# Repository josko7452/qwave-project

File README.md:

QWave-project
=============

Working FPGA development board with USB 2.0 interface and DSO module (125MHz analog dual channel with 16bit logic analyzer)
Although hadware was implemented it is not thoroughly tested, especially analog part is not intented as ready to build kit, it is inteded for hackers and people who are wiling to play around to get it working.

# Project parts
* **hardware** design sources of FPGA developement board and DSO module in eagle
* **firmware** sources of FPGA firmware in MyHDL and translated VHDL Xinix ISE project directory
* **software** sources of Qt based DSO sampling software

# Preview
## FPGA dev board and DSO module (dimensions 10x4cm):
-
## Software
[Screenshot gallery](http://imgur.com/a/RICwH#0)

#Schematics
[Link to PDF](https://www.dropbox.com/sh/cy4ldah24slzdpa/zRzbHfkyo1)

#Details:
## FPGA board:
### What works:
* FPGA programming and 3.3V logic interface and FT245 Sync interface (USB 2.0 speed)

### TODO:
* Direct USB programming of FPGA flash - need to use JTAG and Xilinx USB Platform Cable for programming

## Analog (DSO module) board:
### What works:
* DSO functionality

### What was not tested:
* Logic analyzer on anything faster than few kHz
* Compensation of analog input

### TODO:
* Eliminating noise on analog circuits

## Firmware
### TODO:
* Fix trigger
* Add selectable trigger holdoff
* Do not insert trigger in single-shot mode

## Software
### TODO:
* Better performance
* Make more user-friendly selection of trigger
* Add exact voltage meter

## For hackers/ee guys and developers:
See HACKING.md

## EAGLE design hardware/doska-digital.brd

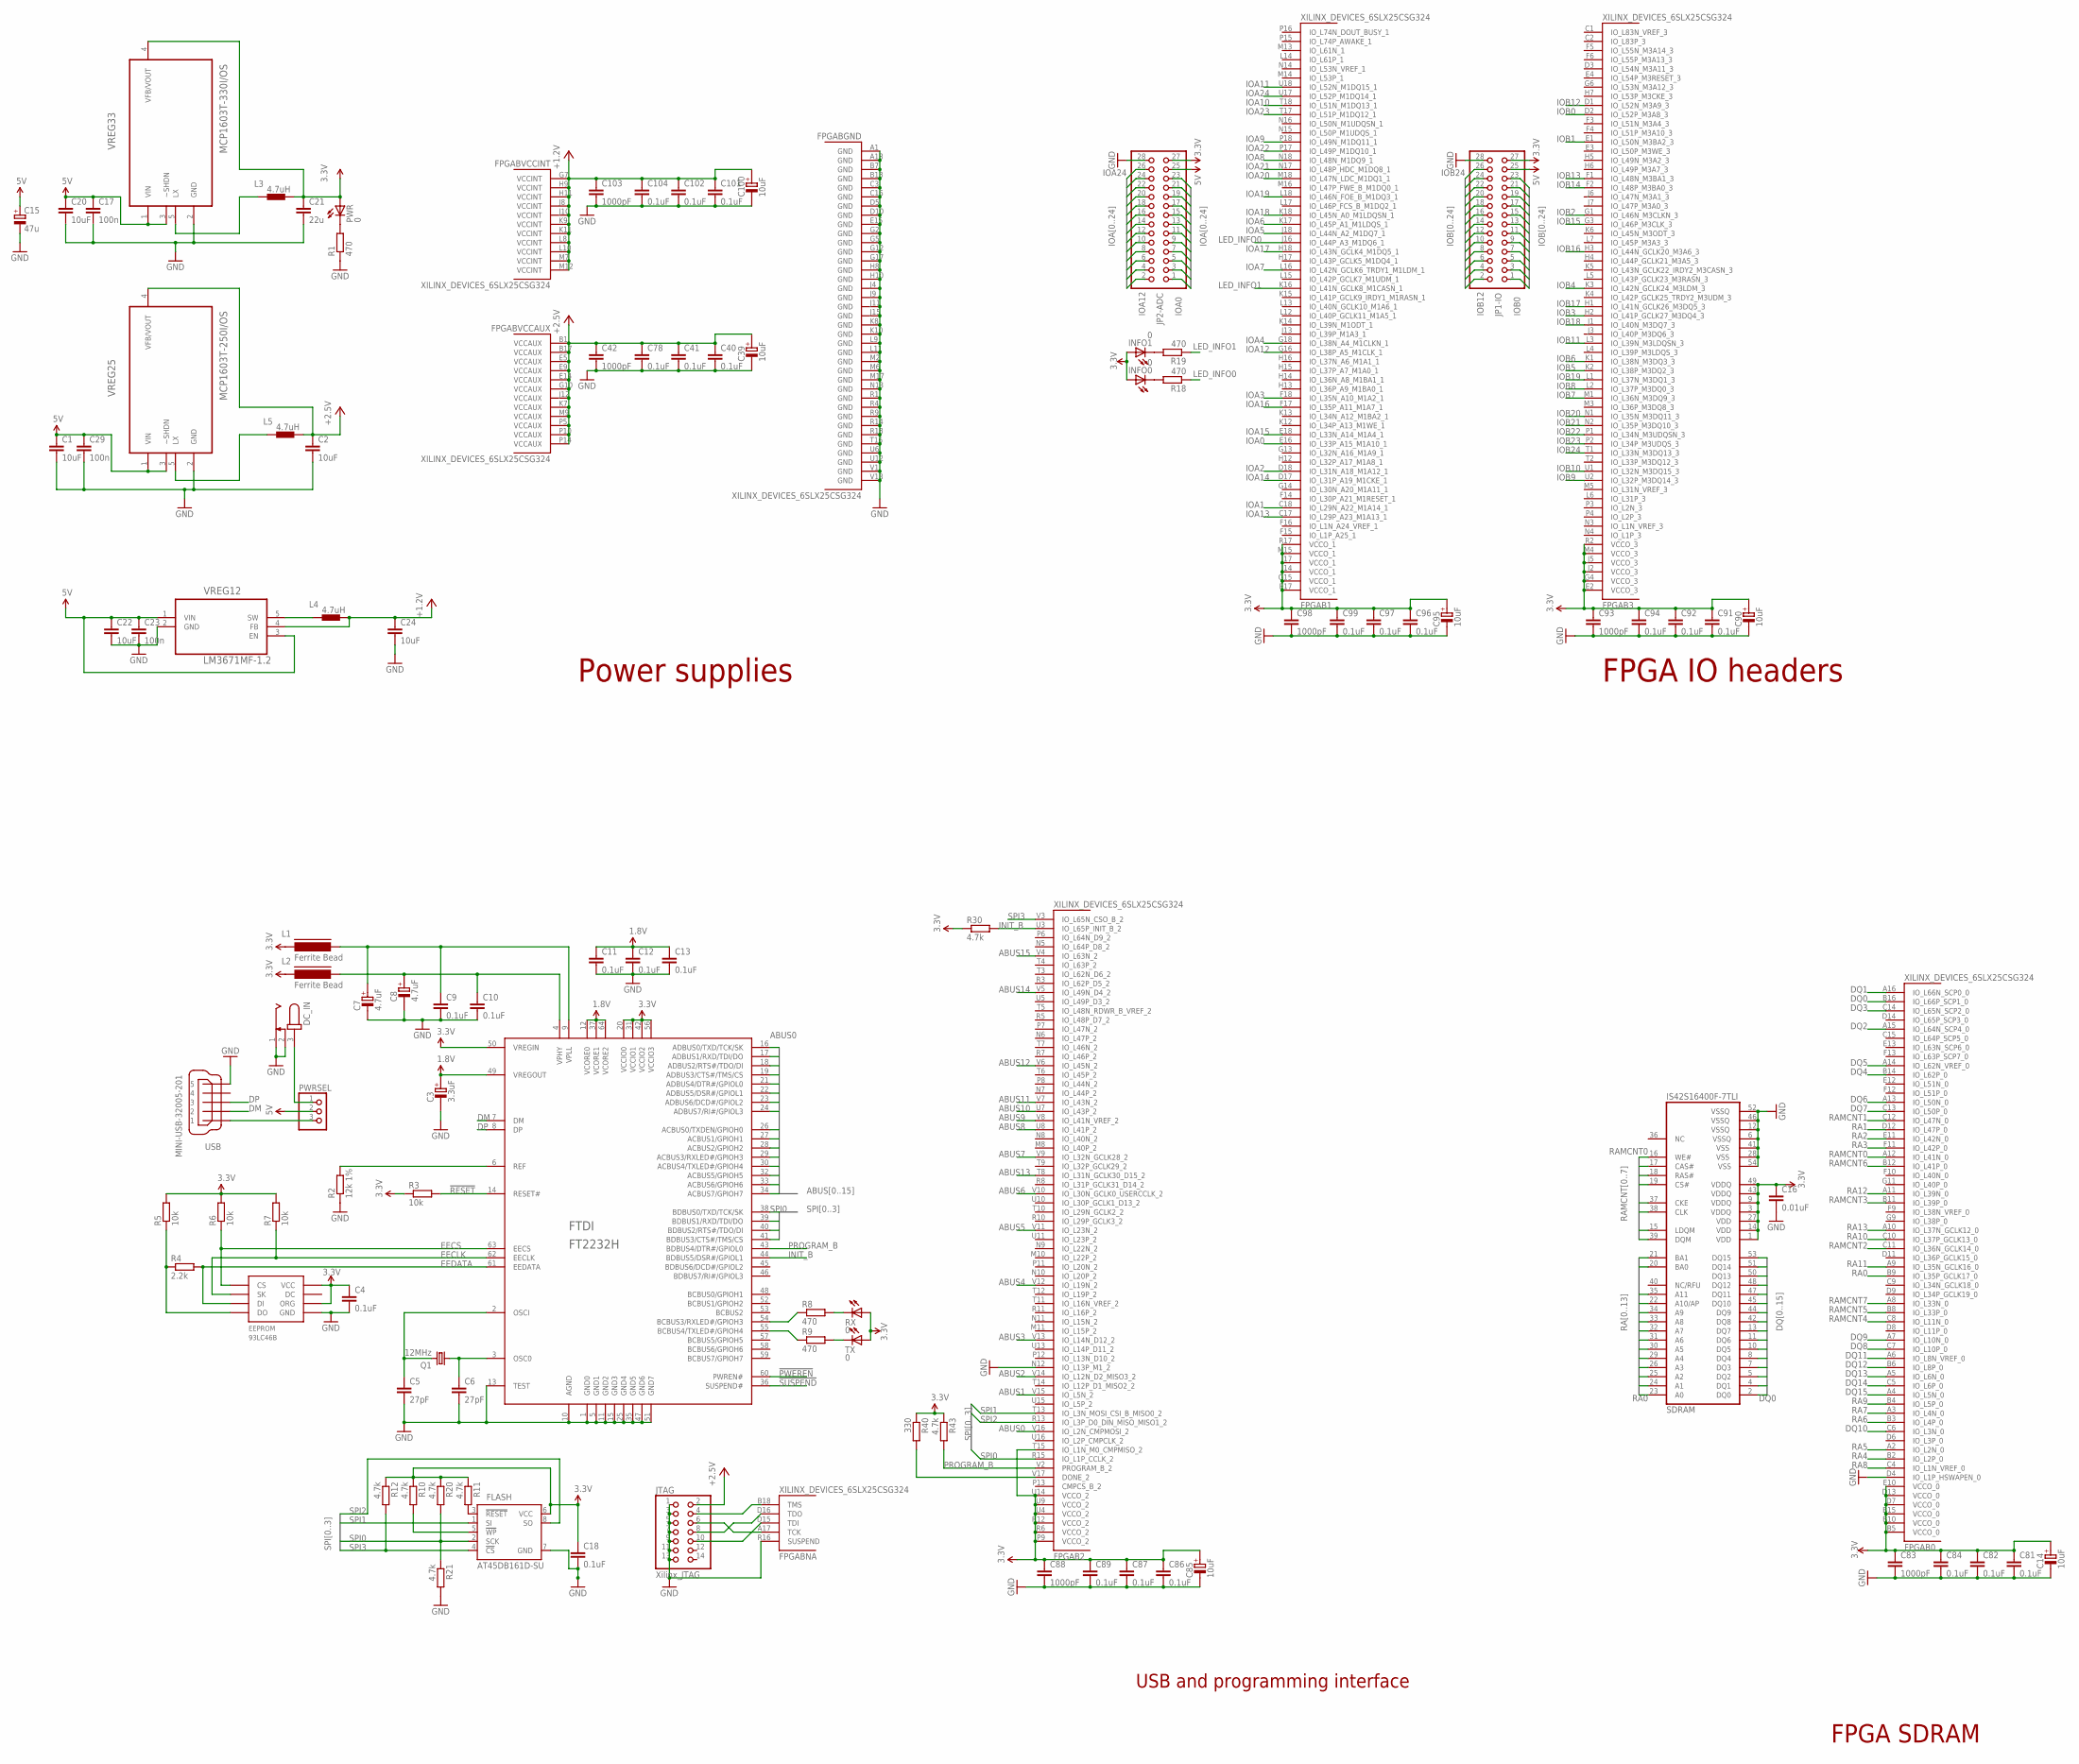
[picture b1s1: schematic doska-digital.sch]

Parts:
C1, C2, C20, C22, C24: 10uF; C805
C3: 3.3uF; CAPMP3216X180N
C4, C13, C18: 0.1uF; C805
C5, C6: 27pF; C805
C7, C8: 4.7uF; CAPMP3216X180N
C9, C10, C11, C12, C40, C41, C78, C81, C82, C84, C86, C87, C89, C91, C92, C94, C96, C97, C99, C101, C102, C104: 0.1uF; C603
C14, C39, C85, C90, C95, C100: 10uF; CAPMP3216X180N
C15: 47u; RCL_E2-5
C16: 0.01uF; C805
C17, C23, C29: 100n; C805
C21: 22u; C805
C42, C83, C88, C93, C98, C103: 1000pF; C603
DC_IN: CON-JACK_JACK-PLUG1; CON-JACK_SPC4078
EEPROM: 93LC46B; SOIC8
FLASH: AT45DB161D-SU; 8S2
FPGA: XILINX_DEVICES_6SLX25CSG324; XILINX_DEVICES_CS324
FTDI: FT2232H; LQFP64
INFO0, INFO1: 0; CHIPLED_1206
JP1-IO, JP2-ADC: PINHEAD_PINHD-2X14; PINHEAD_2X14
JTAG: Xilinx_JTAG; PINHEAD_2X07
L1, L2: Ferrite Bead; FB805
L3, L4, L5: 4.7uH; SMT43
PWR: 0; CHIPLED_1206
PWRSEL: PINHEAD_PINHD-1X3; PINHEAD_1X03
Q1: 12MHz; CTS406
R1, R8, R9, R18, R19: 470; R805
R2: 12k 1%; R603
R3, R5, R6, R7: 10k; R805
R4: 2.2k; R805
R10, R11, R12: 4.7k; R805
R20, R21, R30, R43: 4.7k; R603
R40: 330; R603
RX: 0; CHIPLED_1206
SDRAM: IS42S16400F-7TLI; TSOP54
TX: 0; CHIPLED_1206
USB: MINI-USB-32005-201; 32005-201
VREG12: LM3671MF-1.2; SOT95P284X122-5N
VREG25: MCP1603T-250I/OS; SOT95P280X110-5N
VREG33: MCP1603T-330I/OS; SOT95P280X110-5N

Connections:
1.8V: C3.+, C11.1, C12.1, C13.1, FTDI.12 (VCORE0), FTDI.37 (VCORE1), FTDI.49 (VREGOUT), FTDI.64 (VCORE2)
3.3V: C4.1, C14.+, C16.1, C18.1, C21.1, C81.1, C82.1, C83.1, C84.1, C85.+, C86.1, C87.1, C88.1, C89.1, C90.+, C91.1, C92.1, C93.1, C94.1, C95.+, C96.1, C97.1, C98.1, C99.1, EEPROM.6 (ORG), EEPROM.8 (VCC), FLASH.6 (VCC), FPGA.B5 (VCCO_0), FPGA.B10 (VCCO_0), FPGA.B15 (VCCO_0), FPGA.D7 (VCCO_0), FPGA.D13 (VCCO_0), FPGA.E2 (VCCO_3), FPGA.E10 (VCCO_0), FPGA.E17 (VCCO_1), FPGA.G4 (VCCO_3), FPGA.G15 (VCCO_1), FPGA.J2 (VCCO_3), FPGA.J5 (VCCO_3), FPGA.J14 (VCCO_1), FPGA.J17 (VCCO_1), FPGA.M4 (VCCO_3), FPGA.M15 (VCCO_1), FPGA.P9 (VCCO_2), FPGA.R2 (VCCO_3), FPGA.R6 (VCCO_2), FPGA.R12 (VCCO_2), FPGA.R17 (VCCO_1), FPGA.T15 (IO_L1N_M0_CMPMISO_2), FPGA.U4 (VCCO_2), FPGA.U9 (VCCO_2), FPGA.U14 (VCCO_2), FTDI.20 (VCCIO0), FTDI.31 (VCCIO1), FTDI.42 (VCCIO2), FTDI.50 (VREGIN), FTDI.56 (VCCIO3), INFO0.A, INFO1.A, JP1-IO.27, JP2-ADC.27, L1.2, L2.2, L3.P$1 (1), PWR.A, R3.1, R5.2, R6.2, R7.2, R10.1, R11.1, R12.1, R20.1, R30.1, R40.1, R43.1, RX.A, SDRAM.1 (VDD), SDRAM.3 (VDDQ), SDRAM.9 (VDDQ), SDRAM.14 (VDD), SDRAM.27 (VDD), SDRAM.43 (VDDQ), SDRAM.49 (VDDQ), TX.A, VREG33.4 (VFB/VOUT)
5V: C1.1, C15.+, C17.1, C20.1, C22.1, C23.1, C29.1, JP1-IO.25, JP2-ADC.25, PWRSEL.2, VREG12.1 (VIN), VREG12.3 (EN), VREG25.1 (VIN), VREG25.3 (~SHDN), VREG33.1 (VIN), VREG33.3 (~SHDN)
!PWEREN: FTDI.60 (PWREN#)
!RESET: FTDI.14 (RESET#), R3.2
!SUSPEND: FTDI.36 (SUSPEND#)
+1.2V: C24.1, C100.+, C101.1, C102.1, C103.1, C104.1, FPGA.G7 (VCCINT), FPGA.H9 (VCCINT), FPGA.H11 (VCCINT), FPGA.J8 (VCCINT), FPGA.J10 (VCCINT), FPGA.K9 (VCCINT), FPGA.K11 (VCCINT), FPGA.L8 (VCCINT), FPGA.L10 (VCCINT), FPGA.M7 (VCCINT), FPGA.M12 (VCCINT), L4.P$1 (1), VREG12.4 (FB)
+2.5V: C2.1, C39.+, C40.1, C41.1, C42.1, C78.1, FPGA.B1 (VCCAUX), FPGA.B17 (VCCAUX), FPGA.E5 (VCCAUX), FPGA.E9 (VCCAUX), FPGA.E14 (VCCAUX), FPGA.G10 (VCCAUX), FPGA.J12 (VCCAUX), FPGA.K7 (VCCAUX), FPGA.M9 (VCCAUX), FPGA.P5 (VCCAUX), FPGA.P10 (VCCAUX), FPGA.P14 (VCCAUX), JTAG.2, L5.P$1 (1), VREG25.4 (VFB/VOUT)
ABUS0: FPGA.V16 (IO_L2N_CMPMOSI_2), FTDI.16 (ADBUS0/TXD/TCK/SK)
ABUS1: FPGA.V15 (IO_L5N_2), FTDI.17 (ADBUS1/RXD/TDI/DO)
ABUS2: FPGA.V14 (IO_L12N_D2_MISO3_2), FTDI.18 (ADBUS2/RTS#/TDO/DI)
ABUS3: FPGA.V13 (IO_L14N_D12_2), FTDI.19 (ADBUS3/CTS#/TMS/CS)
ABUS4: FPGA.V12 (IO_L19N_2), FTDI.21 (ADBUS4/DTR#/GPIOL0)
ABUS5: FPGA.V11 (IO_L23N_2), FTDI.22 (ADBUS5/DSR#/GPIOL1)
ABUS6: FPGA.V10 (IO_L30N_GCLK0_USERCCLK_2), FTDI.23 (ADBUS6/DCD#/GPIOL2)
ABUS7: FPGA.V9 (IO_L32N_GCLK28_2), FTDI.24 (ADBUS7/RI#/GPIOL3)
ABUS8: FPGA.U8 (IO_L41P_2), FTDI.26 (ACBUS0/TXDEN/GPIOH0)
ABUS9: FPGA.V8 (IO_L41N_VREF_2), FTDI.27 (ACBUS1/GPIOH1)
ABUS10: FPGA.U7 (IO_L43P_2), FTDI.28 (ACBUS2/GPIOH2)
ABUS11: FPGA.V7 (IO_L43N_2), FTDI.29 (ACBUS3/RXLED#/GPIOH3)
ABUS12: FPGA.V6 (IO_L45N_2), FTDI.30 (ACBUS4/TXLED#/GPIOH4)
ABUS13: FPGA.T8 (IO_L31N_GCLK30_D15_2), FTDI.32 (ACBUS5/GPIOH5)
ABUS14: FPGA.V5 (IO_L49N_D4_2), FTDI.33 (ACBUS6/GPIOH6)
ABUS15: FPGA.V4 (IO_L63N_2), FTDI.34 (ACBUS7/GPIOH7)
DM: FTDI.7 (DM), USB.2
DP: FTDI.8 (DP), USB.3
DQ0: FPGA.B16 (IO_L66P_SCP1_0), SDRAM.2 (DQ0)
DQ1: FPGA.A16 (IO_L66N_SCP0_0), SDRAM.4 (DQ1)
DQ2: FPGA.A15 (IO_L64N_SCP4_0), SDRAM.5 (DQ2)
DQ3: FPGA.C14 (IO_L65N_SCP2_0), SDRAM.7 (DQ3)
DQ4: FPGA.B14 (IO_L62P_0), SDRAM.8 (DQ4)
DQ5: FPGA.A14 (IO_L62N_VREF_0), SDRAM.10 (DQ5)
DQ6: FPGA.A13 (IO_L50N_0), SDRAM.11 (DQ6)
DQ7: FPGA.C13 (IO_L50P_0), SDRAM.13 (DQ7)
DQ8: FPGA.C7 (IO_L10P_0), SDRAM.42 (DQ8)
DQ9: FPGA.A7 (IO_L10N_0), SDRAM.44 (DQ9)
DQ10: FPGA.C6 (IO_L3N_0), SDRAM.45 (DQ10)
DQ11: FPGA.A6 (IO_L8N_VREF_0), SDRAM.47 (DQ11)
DQ12: FPGA.B6 (IO_L8P_0), SDRAM.48 (DQ12)
DQ13: FPGA.A5 (IO_L6N_0), SDRAM.50 (DQ13)
DQ14: FPGA.C5 (IO_L6P_0), SDRAM.51 (DQ14)
DQ15: FPGA.A4 (IO_L5N_0), SDRAM.53 (DQ15)
EECLK: EEPROM.2 (SK), FTDI.62 (EECLK), R7.1
EECS: EEPROM.1 (CS), FTDI.63 (EECS), R6.1
EEDATA: EEPROM.3 (DI), FTDI.61 (EEDATA), R4.2
GND: C1.2, C2.2, C3.-, C4.2, C5.2, C6.2, C7.-, C8.-, C9.2, C10.2, C11.2, C12.2, C13.2, C14.-, C15.-, C16.2, C17.2, C18.2, C20.2, C21.2, C22.2, C23.2, C24.2, C29.2, C39.-, C40.2, C41.2, C42.2, C78.2, C81.2, C82.2, C83.2, C84.2, C85.-, C86.2, C87.2, C88.2, C89.2, C90.-, C91.2, C92.2, C93.2, C94.2, C95.-, C96.2, C97.2, C98.2, C99.2, C100.-, C101.2, C102.2, C103.2, C104.2, DC_IN.1, DC_IN.2, EEPROM.5 (GND), FLASH.7 (GND), FPGA.A1 (GND), FPGA.A18 (GND), FPGA.B7 (GND), FPGA.B13 (GND), FPGA.C3 (GND), FPGA.C16 (GND), FPGA.D4 (IO_L1P_HSWAPEN_0), FPGA.D5 (GND), FPGA.D10 (GND), FPGA.E15 (GND), FPGA.G2 (GND), FPGA.G5 (GND), FPGA.G12 (GND), FPGA.G17 (GND), FPGA.H8 (GND), FPGA.H10 (GND), FPGA.J4 (GND), FPGA.J9 (GND), FPGA.J11 (GND), FPGA.J15 (GND), FPGA.K8 (GND), FPGA.K10 (GND), FPGA.L9 (GND), FPGA.L11 (GND), FPGA.M2 (GND), FPGA.M6 (GND), FPGA.M17 (GND), FPGA.N12 (IO_L13P_M1_2), FPGA.N13 (GND), FPGA.R1 (GND), FPGA.R4 (GND), FPGA.R9 (GND), FPGA.R14 (GND), FPGA.R16 (SUSPEND), FPGA.R18 (GND), FPGA.T16 (GND), FPGA.U6 (GND), FPGA.U12 (GND), FPGA.V1 (GND), FPGA.V18 (GND), FTDI.1 (GND0), FTDI.5 (GND1), FTDI.10 (AGND), FTDI.11 (GND2), FTDI.13 (TEST), FTDI.15 (GND3), FTDI.25 (GND4), FTDI.35 (GND5), FTDI.47 (GND6), FTDI.51 (GND7), JP1-IO.28, JP2-ADC.28, JTAG.1, JTAG.3, JTAG.5, JTAG.7, JTAG.9, JTAG.11, JTAG.13, R1.1, R2.1, R21.2, SDRAM.6 (VSSQ), SDRAM.12 (VSSQ), SDRAM.28 (VSS), SDRAM.41 (VSS), SDRAM.46 (VSSQ), SDRAM.52 (VSSQ), SDRAM.54 (VSS), USB.5, VREG12.2 (GND), VREG25.2 (GND), VREG33.2 (GND)
INIT_B: FPGA.U3 (IO_L65P_INIT_B_2), FTDI.44 (BDBUS5/DSR#/GPIOL1), R30.2
IOA0: FPGA.E16 (IO_L33P_A15_M1A10_1), JP2-ADC.1
IOA1: FPGA.C18 (IO_L29N_A22_M1A14_1), JP2-ADC.3
IOA2: FPGA.D18 (IO_L31N_A18_M1A12_1), JP2-ADC.5
IOA3: FPGA.F18 (IO_L35N_A10_M1A2_1), JP2-ADC.7
IOA4: FPGA.G18 (IO_L38N_A4_M1CLKN_1), JP2-ADC.9
IOA5: FPGA.J18 (IO_L44N_A2_M1DQ7_1), JP2-ADC.11
IOA6: FPGA.K17 (IO_L45P_A1_M1LDQS_1), JP2-ADC.13
IOA7: FPGA.L16 (IO_L42N_GCLK6_TRDY1_M1LDM_1), JP2-ADC.15
IOA8: FPGA.N18 (IO_L48N_M1DQ9_1), JP2-ADC.17
IOA9: FPGA.P18 (IO_L49N_M1DQ11_1), JP2-ADC.19
IOA10: FPGA.T18 (IO_L51N_M1DQ13_1), JP2-ADC.21
IOA11: FPGA.U18 (IO_L52N_M1DQ15_1), JP2-ADC.23
IOA12: FPGA.G16 (IO_L38P_A5_M1CLK_1), JP2-ADC.2
IOA13: FPGA.C17 (IO_L29P_A23_M1A13_1), JP2-ADC.4
IOA14: FPGA.D17 (IO_L31P_A19_M1CKE_1), JP2-ADC.6
IOA15: FPGA.E18 (IO_L33N_A14_M1A4_1), JP2-ADC.8
IOA16: FPGA.F17 (IO_L35P_A11_M1A7_1), JP2-ADC.10
IOA17: FPGA.H18 (IO_L43N_GCLK4_M1DQ5_1), JP2-ADC.12
IOA18: FPGA.K18 (IO_L45N_A0_M1LDQSN_1), JP2-ADC.14
IOA19: FPGA.L18 (IO_L46N_FOE_B_M1DQ3_1), JP2-ADC.16
IOA20: FPGA.M18 (IO_L47N_LDC_M1DQ1_1), JP2-ADC.18
IOA21: FPGA.N17 (IO_L48P_HDC_M1DQ8_1), JP2-ADC.20
IOA22: FPGA.P17 (IO_L49P_M1DQ10_1), JP2-ADC.22
IOA23: FPGA.T17 (IO_L51P_M1DQ12_1), JP2-ADC.24
IOA24: FPGA.U17 (IO_L52P_M1DQ14_1), JP2-ADC.26
IOB0: FPGA.D2 (IO_L52P_M3A8_3), JP1-IO.1
IOB1: FPGA.E1 (IO_L50N_M3BA2_3), JP1-IO.3
IOB2: FPGA.G1 (IO_L46N_M3CLKN_3), JP1-IO.5
IOB3: FPGA.H2 (IO_L41P_GCLK27_M3DQ4_3), JP1-IO.7
IOB4: FPGA.K3 (IO_L42N_GCLK24_M3LDM_3), JP1-IO.9
IOB5: FPGA.K2 (IO_L38P_M3DQ2_3), JP1-IO.11
IOB6: FPGA.K1 (IO_L38N_M3DQ3_3), JP1-IO.13
IOB7: FPGA.M1 (IO_L36N_M3DQ9_3), JP1-IO.15
IOB8: FPGA.L2 (IO_L37P_M3DQ0_3), JP1-IO.17
IOB9: FPGA.U2 (IO_L32P_M3DQ14_3), JP1-IO.19
IOB10: FPGA.U1 (IO_L32N_M3DQ15_3), JP1-IO.21
IOB11: FPGA.L3 (IO_L39N_M3LDQSN_3), JP1-IO.23
IOB12: FPGA.D1 (IO_L52N_M3A9_3), JP1-IO.2
IOB13: FPGA.F1 (IO_L48N_M3BA1_3), JP1-IO.4
IOB14: FPGA.F2 (IO_L48P_M3BA0_3), JP1-IO.6
IOB15: FPGA.G3 (IO_L46P_M3CLK_3), JP1-IO.8
IOB16: FPGA.H3 (IO_L44N_GCLK20_M3A6_3), JP1-IO.10
IOB17: FPGA.H1 (IO_L41N_GCLK26_M3DQ5_3), JP1-IO.12
IOB18: FPGA.J1 (IO_L40N_M3DQ7_3), JP1-IO.14
IOB19: FPGA.L1 (IO_L37N_M3DQ1_3), JP1-IO.16
IOB20: FPGA.N1 (IO_L35N_M3DQ11_3), JP1-IO.18
IOB21: FPGA.N2 (IO_L35P_M3DQ10_3), JP1-IO.20
IOB22: FPGA.P1 (IO_L34N_M3UDQSN_3), JP1-IO.22
IOB23: FPGA.P2 (IO_L34P_M3UDQS_3), JP1-IO.24
IOB24: FPGA.T1 (IO_L33N_M3DQ13_3), JP1-IO.26
LED_INFO0: FPGA.J16 (IO_L44P_A3_M1DQ6_1), R18.1
LED_INFO1: FPGA.K16 (IO_L41N_GCLK8_M1CASN_1), R19.1
unnamed: PWR.C, R1.2
unnamed: R8.2, RX.C
unnamed: R9.2, TX.C
unnamed: FTDI.6 (REF), R2.2
unnamed: FLASH.5 (!WP), R10.2
unnamed: FLASH.3 (!RESET), R11.2
unnamed: C5.1, FTDI.2 (OSCI), Q1.3 (2)
unnamed: C6.1, FTDI.3 (OSC0), Q1.1
unnamed: L4.P$2 (2), VREG12.5 (SW)
unnamed: INFO0.C, R18.2
unnamed: L5.P$2 (2), VREG25.5 (LX)
unnamed: PWRSEL.3, USB.1
unnamed: L3.P$2 (2), VREG33.5 (LX)
unnamed: DC_IN.3, PWRSEL.1
unnamed: INFO1.C, R19.2
unnamed: FTDI.55 (BCBUS4/TXLED#/GPIOH4), R9.1
unnamed: FTDI.54 (BCBUS3/RXLED#/GPIOH3), R8.1
unnamed: FPGA.V17 (DONE_2), R40.2
unnamed: FPGA.B18 (TMS), JTAG.4
unnamed: FPGA.A17 (TCK), JTAG.6
unnamed: EEPROM.4 (DO), R4.1, R5.1
unnamed: FPGA.D16 (TDO), JTAG.8
unnamed: FPGA.D15 (TDI), JTAG.10
unnamed: C7.+, C9.1, FTDI.9 (VPLL), L1.1
unnamed: C8.+, C10.1, FTDI.4 (VPHY), L2.1
PROGRAM_B: FPGA.V2 (PROGRAM_B_2), FTDI.43 (BDBUS4/DTR#/GPIOL0), R43.2
RA0: FPGA.B9 (IO_L35P_GCLK17_0), SDRAM.23 (A0)
RA1: FPGA.D12 (IO_L47P_0), SDRAM.24 (A1)
RA2: FPGA.E11 (IO_L42N_0), SDRAM.25 (A2)
RA3: FPGA.F11 (IO_L42P_0), SDRAM.26 (A3)
RA4: FPGA.B2 (IO_L2P_0), SDRAM.29 (A4)
RA5: FPGA.A2 (IO_L2N_0), SDRAM.30 (A5)
RA6: FPGA.B3 (IO_L4P_0), SDRAM.31 (A6)
RA7: FPGA.A3 (IO_L4N_0), SDRAM.32 (A7)
RA8: FPGA.C4 (IO_L1N_VREF_0), SDRAM.33 (A8)
RA9: FPGA.B4 (IO_L5P_0), SDRAM.34 (A9)
RA10: FPGA.C10 (IO_L37P_GCLK13_0), SDRAM.22 (A10/AP)
RA11: FPGA.A9 (IO_L35N_GCLK16_0), SDRAM.35 (A11)
RA12: FPGA.A11 (IO_L39N_0), SDRAM.20 (BA0)
RA13: FPGA.A10 (IO_L37N_GCLK12_0), SDRAM.21 (BA1)
RAMCNT0: FPGA.A12 (IO_L41N_0), SDRAM.16 (WE#)
RAMCNT1: FPGA.C12 (IO_L47N_0), SDRAM.17 (CAS#)
RAMCNT2: FPGA.C11 (IO_L36N_GCLK14_0), SDRAM.18 (RAS#)
RAMCNT3: FPGA.B11 (IO_L39P_0), SDRAM.19 (CS#)
RAMCNT4: FPGA.C8 (IO_L11N_0), SDRAM.37 (CKE)
RAMCNT5: FPGA.B8 (IO_L33P_0), SDRAM.38 (CLK)
RAMCNT6: FPGA.B12 (IO_L41P_0), SDRAM.15 (LDQM)
RAMCNT7: FPGA.A8 (IO_L33N_0), SDRAM.39 (DQM)
SPI0: FLASH.2 (SCK), FPGA.R15 (IO_L1P_CCLK_2), FTDI.38 (BDBUS0/TXD/TCK/SK), R20.2, R21.1
SPI1: FLASH.1 (SI), FPGA.T13 (IO_L3N_MOSI_CSI_B_MISO0_2), FTDI.39 (BDBUS1/RXD/TDI/DO)
SPI2: FLASH.8 (SO), FPGA.R13 (IO_L3P_D0_DIN_MISO_MISO1_2), FTDI.40 (BDBUS2/RTS#/TDO/DI)
SPI3: FLASH.4 (!CS), FPGA.V3 (IO_L65N_CSO_B_2), FTDI.41 (BDBUS3/CTS#/TMS/CS), R12.2

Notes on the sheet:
FPGA IO headers
FPGA SDRAM
Power supplies
USB and programming interface

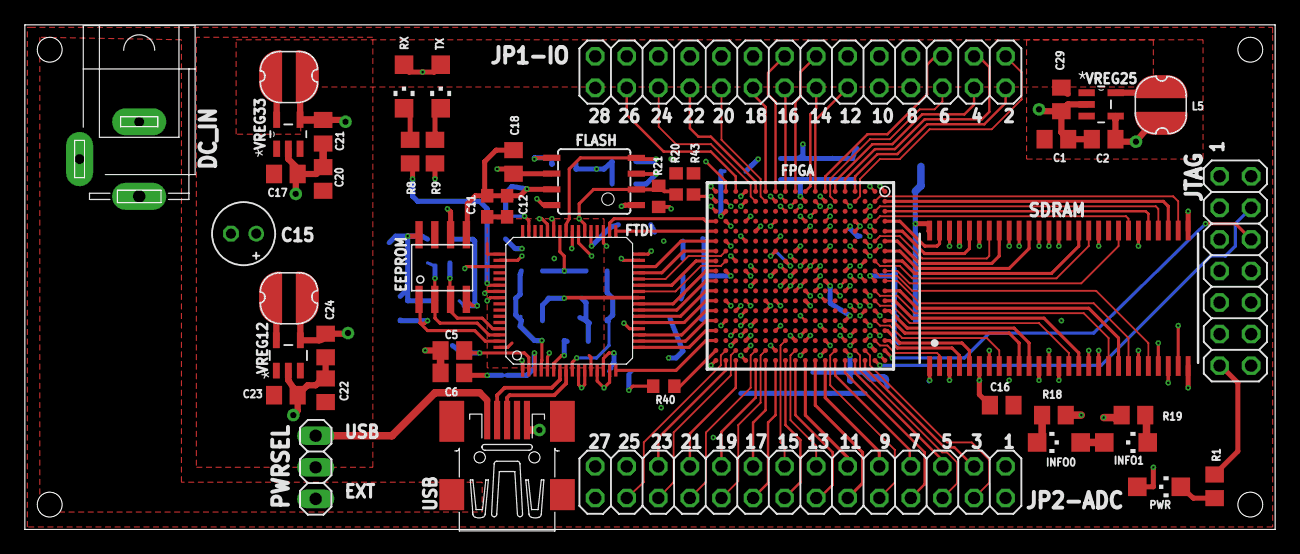
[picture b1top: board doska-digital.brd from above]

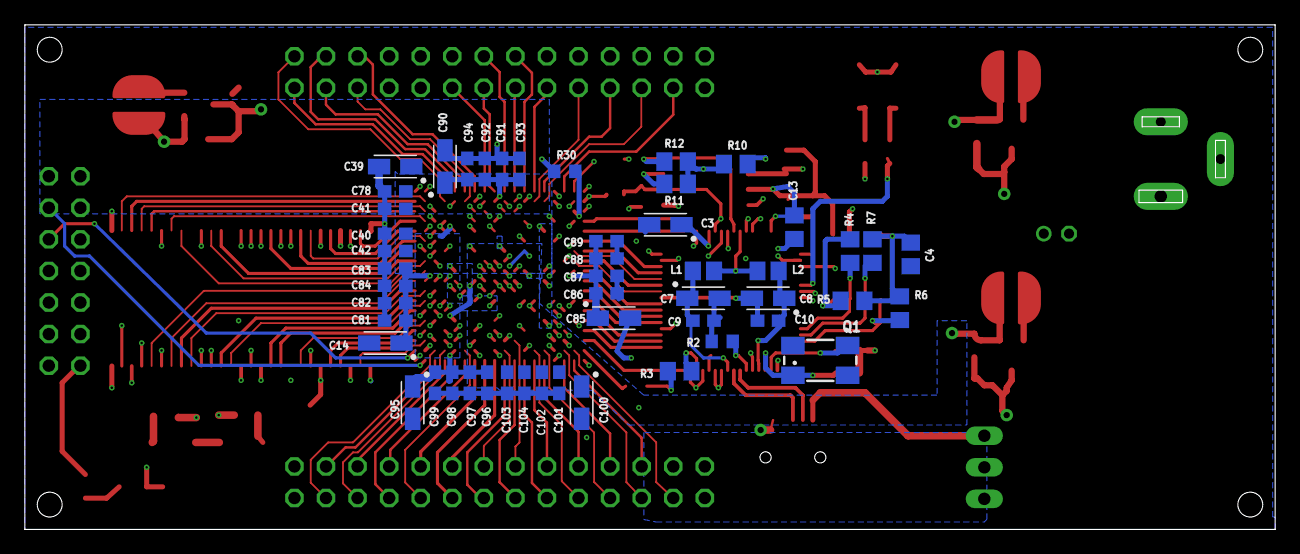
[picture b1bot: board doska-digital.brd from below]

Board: 4 copper layers, 100.6 x 40.6 mm, 97 parts (50 on the bottom side), 149 nets.

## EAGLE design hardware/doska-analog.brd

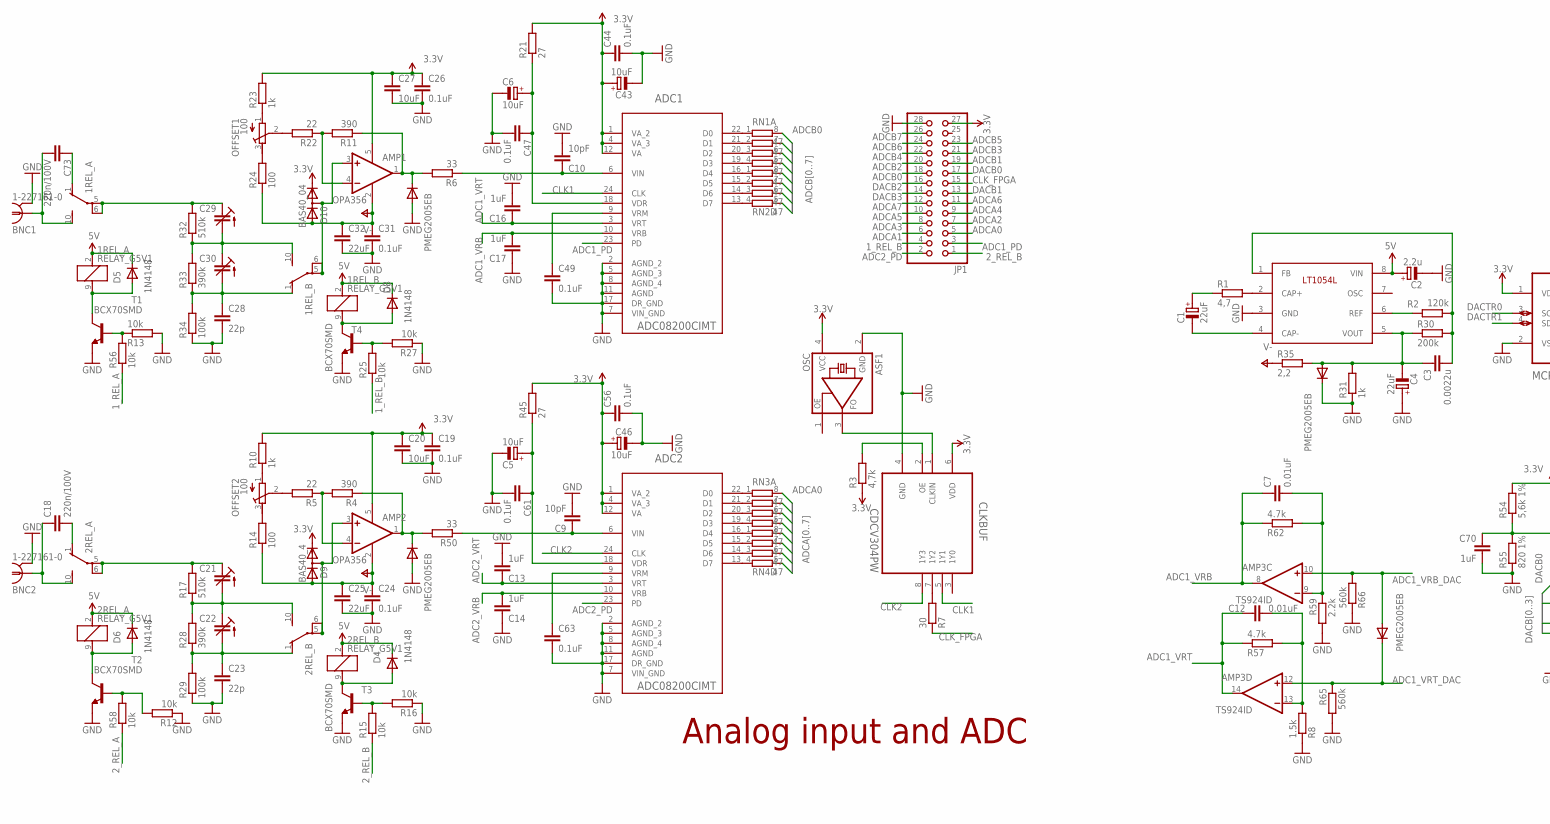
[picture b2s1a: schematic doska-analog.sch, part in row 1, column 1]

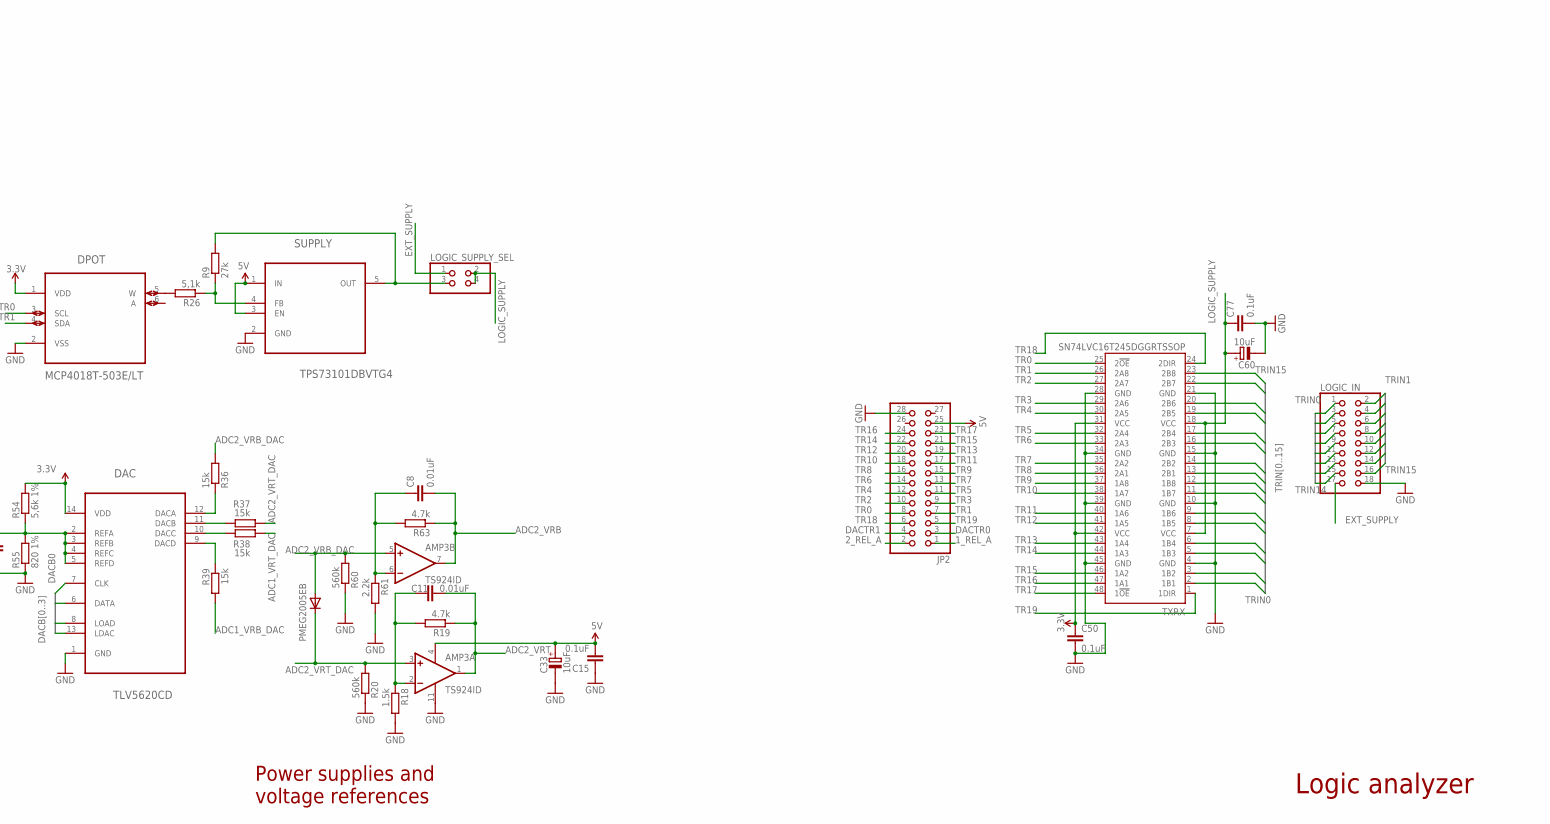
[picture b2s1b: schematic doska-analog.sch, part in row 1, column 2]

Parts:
1REL_A, 2REL_A: RELAY_G5V1
1REL_B, 2REL_B: RELAY_G5V1; MPN G5V-1-DC24
ADC1, ADC2: ADC08200CIMT; SOP65P640X110-24N
AMP1, AMP2: OPA356; SOT23-5
AMP3: TS924ID; SOIC127P600X175-14N
BNC1, BNC2: 1-227161-0; AMP_227161
C1, C4: 22uF; CAPMP3528X210N
C2: 2.2u; CAPMP3216X180N
C3: 0.0022u; C603
C5, C6, C33, C43, C46, C60: 10uF; CAPMP3216X180N
C7, C8, C11, C12: 0.01uF; C603
C9, C10: 10pF; C603
C13, C14, C16, C17, C70: 1uF; C603
C15, C50, C77: 0.1uF; C805
C18, C73: 220n/100V; C1206
C19, C24, C26, C31, C44, C47, C49, C56, C61, C63: 0.1uF; C603
C20, C27: 10uF; C805
C21, C22, C29, C30: TZB4Z100AB10R00; CTRIMTZB4
C23, C28: 22p; C603
C25, C32: 22uF; C805
CLKBUF: CDCV304PW; SOP65P640X120-8N
D1, D2, D3, D7, D11: PMEG2005EB; SOD523
D4, D5, D6, D8: 1N4148; SOD323-R
D9: BAS40_4; SOT23
D10: BAS40_04; SOT23
DAC: TLV5620CD; SOIC127P600X175-14N
DPOT: MCP4018T-503E/LT; SOT65P210X110-6N
JP1, JP2: PINHEAD_PINHD-2X14; PINHEAD_2X14
LOGIC_IN: PINHEAD_PINHD-2X9; PINHEAD_2X09
LOGIC_SUPPLY_SEL: PINHEAD_PINHD-2X2; PINHEAD_2X02
OFFSET1, OFFSET2: 100; RTRIMTC33
OSC: ASF1; ASF
R1: 4,7; R1206
R2: 120k; R603
R3: 4,7k; R603
R4, R11: 390; R603
R5, R22: 22; R603
R6, R50: 33; R603
R7: 30; R603
R8, R18: 1.5k; R603
R9: 27k; R603
R10, R23, R31: 1k; R603
R12, R13, R15, R16, R25, R27, R56, R58: 10k; R603
R14, R24: 100; R603
R17, R32: 510k; R805
R19, R57, R62, R63: 4.7k; R603
R20, R60, R65, R66: 560k; R603
R21, R45: 27; R603
R26: 5,1k; R603
R28, R33: 390k; R805
R29, R34: 100k; R805
R30: 200k; R603
R35: 2,2; R603
R36, R37, R38, R39: 15k; R603
R54: 5,6k 1%; R603
R55: 820 1%; R603
R59, R61: 2.2k; R603
RN1, RN2, RN3, RN4: 47; EXB38V
SUPPLY: TPS73101DBVTG4; SOT95P280X145-5N
T1, T2, T3, T4: BCX70SMD; SOT23
TXRX: SN74LVC16T245DGGRTSSOP; TSSOP48
VREG: LT1054LCS8; SO08

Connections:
1_REL_A: JP2.1, R56.1
1_REL_B: JP1.4, R25.1
2_REL_A: JP2.2, R58.1
2_REL_B: JP1.1, R15.1
3.3V: ADC1.1 (VA_2), ADC1.4 (VA_3), ADC1.12 (VA), ADC2.1 (VA_2), ADC2.4 (VA_3), ADC2.12 (VA), AMP1.5 (V+), AMP2.5 (V+), C19.1, C20.1, C26.1, C27.1, C43.+, C44.1, C46.+, C50.1, C56.1, CLKBUF.6 (VDD), D9.2 (C), D10.2 (C), DAC.14 (VDD), DPOT.1 (VDD), JP1.27, OSC.4 (VCC), R3.1, R10.2, R21.2, R23.2, R45.2, R54.2, TXRX.31 (VCC), TXRX.42 (VCC)
5V: 1REL_A.2 (1), 1REL_B.2 (1), 2REL_A.2 (1), 2REL_B.2 (1), AMP3.4 (V+), C2.+, C15.2, C33.+, D4.C, D5.C, D6.C, D8.C, JP2.25, SUPPLY.1 (IN), SUPPLY.3 (EN), VREG.8 (VIN)
ADC1_PD: ADC1.23 (PD), JP1.3
ADC1_VRB: ADC1.10 (VRB), AMP3.8 (OUT), C7.1, C17.2, R62.1
ADC1_VRB_DAC: AMP3.10 (+IN), D2.A, R39.2, R66.2
ADC1_VRB_DAC_OUT: DAC.9 (DACD), R39.1
ADC1_VRT: ADC1.3 (VRT), AMP3.14 (OUT), C12.1, C16.1, R57.1
ADC1_VRT_DAC: AMP3.12 (+IN), D2.C, R38.1, R65.1
ADC1_VRT_DAC_OUT: DAC.10 (DACC), R38.2
ADC2_PD: ADC2.23 (PD), JP1.2
ADC2_VRB: ADC2.10 (VRB), AMP3.7 (OUT), C8.2, C14.2, R63.1
ADC2_VRB_DAC: AMP3.5 (+IN), D3.A, R36.2, R60.2
ADC2_VRB_DAC_OUT: DAC.12 (DACA), R36.1
ADC2_VRT: ADC2.3 (VRT), AMP3.1 (OUT), C11.2, C13.1, R19.1
ADC2_VRT_DAC: AMP3.3 (+IN), D3.C, R20.2, R37.1
ADC2_VRT_DAC_OUT: DAC.11 (DACB), R37.2
ADCA0: JP1.5, RN3.8 (2)
ADCA1: JP1.6, RN3.7 (2)
ADCA2: JP1.7, RN3.6 (2)
ADCA3: JP1.8, RN3.5 (2)
ADCA4: JP1.9, RN4.8 (2)
ADCA5: JP1.10, RN4.7 (2)
ADCA6: JP1.11, RN4.6 (2)
ADCA7: JP1.12, RN4.5 (2)
ADCB0: JP1.18, RN1.8 (2)
ADCB1: JP1.19, RN1.7 (2)
ADCB2: JP1.20, RN1.6 (2)
ADCB3: JP1.21, RN1.5 (2)
ADCB4: JP1.22, RN2.8 (2)
ADCB5: JP1.23, RN2.7 (2)
ADCB6: JP1.24, RN2.6 (2)
ADCB7: JP1.26, RN2.5 (2)
CLK1: ADC1.24 (CLK), CLKBUF.5 (1Y1)
CLK2: ADC2.24 (CLK), CLKBUF.8 (1Y3)
CLK_FPGA: JP1.15, R7.1
DACB0: DAC.7 (CLK), JP1.17
DACB1: DAC.6 (DATA), JP1.13
DACB2: DAC.8 (LOAD), JP1.16
DACB3: DAC.13 (LDAC), JP1.14
DACTR0: DPOT.3 (SCL), JP2.3
DACTR1: DPOT.4 (SDA), JP2.4
EXT_SUPPLY: LOGIC_IN.17, LOGIC_SUPPLY_SEL.1
GND: ADC1.2 (AGND_2), ADC1.5 (AGND_3), ADC1.7 (VIN_GND), ADC1.8 (AGND_4), ADC1.11 (AGND), ADC1.17 (DR_GND), ADC2.2 (AGND_2), ADC2.5 (AGND_3), ADC2.7 (VIN_GND), ADC2.8 (AGND_4), ADC2.11 (AGND), ADC2.17 (DR_GND), AMP3.11 (V-), BNC1.2 (GND), BNC2.2 (GND), C2.-, C4.+, C5.-, C6.-, C9.2, C10.2, C13.2, C14.1, C15.1, C16.2, C17.1, C19.2, C20.2, C23.2, C24.2, C25.2, C26.2, C27.2, C28.2, C31.2, C32.2, C33.-, C43.-, C44.2, C46.-, C47.2, C49.2, C50.2, C56.2, C60.-, C61.2, C63.2, C70.2, C77.2, CLKBUF.4 (GND), D1.A, D7.A, D11.C, DAC.1 (GND), DPOT.2 (VSS), JP1.28, JP2.28, LOGIC_IN.18, OSC.2 (GND), R8.1, R12.1, R13.2, R16.1, R18.2, R20.1, R27.1, R29.1, R31.1, R34.1, R55.1, R59.2, R60.1, R61.2, R65.2, R66.1, SUPPLY.2 (GND), T1.2 (E), T2.2 (E), T3.2 (E), T4.2 (E), TXRX.4 (GND), TXRX.10 (GND), TXRX.15 (GND), TXRX.21 (GND), TXRX.28 (GND), TXRX.34 (GND), TXRX.39 (GND), TXRX.45 (GND), VREG.3 (GND)
HF_IN: 1REL_A.5, 1REL_A.6, C29.1 (E), R32.2
HF_IN1: 2REL_A.5, 2REL_A.6, C21.1 (E), R17.2
LOGIC_SUPPLY: C60.+, C77.1, LOGIC_SUPPLY_SEL.2, LOGIC_SUPPLY_SEL.4, TXRX.7 (VCC), TXRX.18 (VCC)
unnamed: R1.2, VREG.2 (CAP+)
unnamed: OFFSET1.2 (S), R22.2
unnamed: CLKBUF.2 (OE), R3.2
unnamed: C1.-, VREG.4 (CAP-)
unnamed: CLKBUF.1 (CLKIN), OSC.3 (FO)
unnamed: 2REL_A.1 (O), C18.2
unnamed: AMP2.1 (OUT), D7.C, R4.1, R50.2
unnamed: C1.+, R1.1
unnamed: CLKBUF.7 (1Y2), R7.2
unnamed: OFFSET1.1 (E), R23.1
unnamed: OFFSET1.3 (A), R24.2
unnamed: AMP1.1 (OUT), D1.C, R6.2, R11.1
unnamed: AMP1.4 (-IN), R11.2, R22.1
unnamed: R9.1, R26.1, SUPPLY.4 (FB)
unnamed: DPOT.5 (W), R26.2
unnamed: LOGIC_SUPPLY_SEL.3, R9.2, SUPPLY.5 (OUT)
unnamed: AMP3.9 (-IN), C7.2, R59.1, R62.2
unnamed: R15.2, R16.2, T3.1 (B)
unnamed: OFFSET2.2 (S), R5.2
unnamed: AMP2.4 (-IN), R4.2, R5.1
unnamed: OFFSET2.1 (E), R10.1
unnamed: ADC1.9 (VRM), C49.1
unnamed: ADC1.6 (VIN), C10.1, R6.1
unnamed: OFFSET2.3 (A), R14.2
unnamed: AMP3.13 (-IN), C12.2, R8.2, R57.2
unnamed: 2REL_B.10 (S), C21.2 (A), C22.1 (E), R17.1, R28.2
unnamed: ADC1.18 (VDR), C6.+, C47.1, R21.1
unnamed: 1REL_B.10 (S), C29.2 (A), C30.1 (E), R32.1, R33.2
unnamed: 1REL_B.5, 1REL_B.6, AMP1.3 (+IN), D10.3 (AC)
unnamed: 1REL_B.9 (2), D8.A, T4.3 (C)
unnamed: R25.2, R27.2, T4.1 (B)
unnamed: 1REL_A.1 (O), C73.1
unnamed: 2REL_B.5, 2REL_B.6, AMP2.3 (+IN), D9.3 (AC)
unnamed: R2.1, VREG.6 (REF)
unnamed: 2REL_B.9 (2), D4.A, T3.3 (C)
unnamed: C3.1, C4.-, D11.A, R30.1, R31.2, R35.2, VREG.5 (VOUT)
unnamed: 2REL_B.1 (O), C22.2 (A), C23.1, R28.1, R29.2
unnamed: C3.2, R2.2, R30.2, VREG.1 (FB)
unnamed: 1REL_B.1 (O), C28.1, C30.2 (A), R33.1, R34.2
unnamed: ADC1.22 (D0), RN1.1
unnamed: ADC1.21 (D1), RN1.2 (1)
unnamed: ADC1.20 (D2), RN1.3 (1)
unnamed: ADC2.9 (VRM), C63.1
unnamed: ADC2.6 (VIN), C9.1, R50.1
unnamed: ADC2.18 (VDR), C5.+, C61.1, R45.1
unnamed: ADC1.19 (D3), RN1.4 (1)
unnamed: ADC1.16 (D4), RN2.1
unnamed: ADC1.15 (D5), RN2.2 (1)
unnamed: ADC1.14 (D6), RN2.3 (1)
unnamed: ADC1.13 (D7), RN2.4 (1)
unnamed: ADC2.22 (D0), RN3.1
unnamed: ADC2.21 (D1), RN3.2 (1)
unnamed: C70.1, DAC.2 (REFA), DAC.3 (REFB), DAC.4 (REFC), DAC.5 (REFD), R54.1, R55.2
unnamed: ADC2.20 (D2), RN3.3 (1)
unnamed: ADC2.19 (D3), RN3.4 (1)
unnamed: AMP3.2 (-IN), C11.1, R18.1, R19.2
unnamed: ADC2.16 (D4), RN4.1
unnamed: ADC2.15 (D5), RN4.2 (1)
unnamed: 1REL_A.10 (S), BNC1.1, C73.2
unnamed: AMP3.6 (-IN), C8.1, R61.1, R63.2
unnamed: ADC2.14 (D6), RN4.3 (1)
unnamed: ADC2.13 (D7), RN4.4 (1)
unnamed: 1REL_A.9 (2), D5.A, T1.3 (C)
unnamed: R13.1, R56.2, T1.1 (B)
unnamed: 2REL_A.10 (S), BNC2.1, C18.1
unnamed: 2REL_A.9 (2), D6.A, T2.3 (C)
unnamed: R12.2, R58.2, T2.1 (B)
TR0: JP2.8, TXRX.25 (2!OE)
TR1: JP2.7, TXRX.26 (2A8)
TR2: JP2.10, TXRX.27 (2A7)
TR3: JP2.9, TXRX.29 (2A6)
TR4: JP2.12, TXRX.30 (2A5)
TR5: JP2.11, TXRX.32 (2A4)
TR6: JP2.14, TXRX.33 (2A3)
TR7: JP2.13, TXRX.35 (2A2)
TR8: JP2.16, TXRX.36 (2A1)
TR9: JP2.15, TXRX.37 (1A8)
TR10: JP2.18, TXRX.38 (1A7)
TR11: JP2.17, TXRX.40 (1A6)
TR12: JP2.20, TXRX.41 (1A5)
TR13: JP2.19, TXRX.43 (1A4)
TR14: JP2.22, TXRX.44 (1A3)
TR15: JP2.21, TXRX.46 (1A2)
TR16: JP2.24, TXRX.47 (1A1)
TR17: JP2.23, TXRX.48 (1!OE)
TR18: JP2.6, TXRX.24 (2DIR)
TR19: JP2.5, TXRX.1 (1DIR)
TRIN0: LOGIC_IN.1, TXRX.2 (1B1)
TRIN1: LOGIC_IN.2, TXRX.3 (1B2)
TRIN2: LOGIC_IN.3, TXRX.5 (1B3)
TRIN3: LOGIC_IN.4, TXRX.6 (1B4)
TRIN4: LOGIC_IN.5, TXRX.8 (1B5)
TRIN5: LOGIC_IN.6, TXRX.9 (1B6)
TRIN6: LOGIC_IN.7, TXRX.11 (1B7)
TRIN7: LOGIC_IN.8, TXRX.12 (1B8)
TRIN8: LOGIC_IN.9, TXRX.13 (2B1)
TRIN9: LOGIC_IN.10, TXRX.14 (2B2)
TRIN10: LOGIC_IN.11, TXRX.16 (2B3)
TRIN11: LOGIC_IN.12, TXRX.17 (2B4)
TRIN12: LOGIC_IN.13, TXRX.19 (2B5)
TRIN13: LOGIC_IN.14, TXRX.20 (2B6)
TRIN14: LOGIC_IN.15, TXRX.22 (2B7)
TRIN15: LOGIC_IN.16, TXRX.23 (2B8)
V-: AMP1.2 (V-), AMP2.2 (V-), C24.1, C25.1, C31.1, C32.1, D9.1 (A), D10.1 (A), R14.1, R24.1, R35.1

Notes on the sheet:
Analog input and ADC
Power supplies and voltage references
Logic analyzer

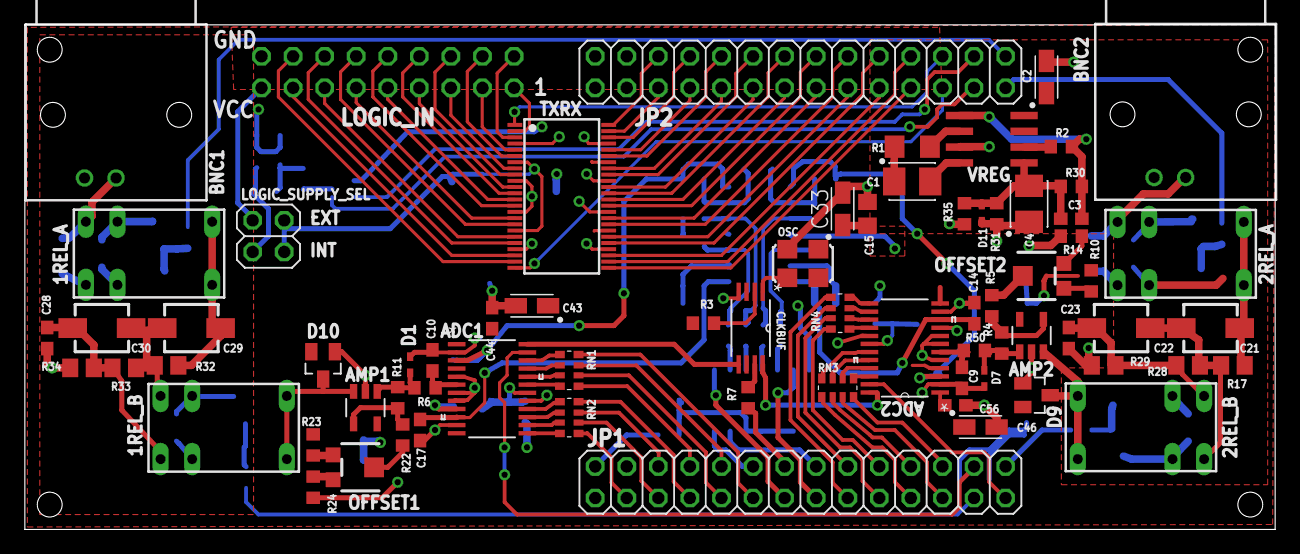
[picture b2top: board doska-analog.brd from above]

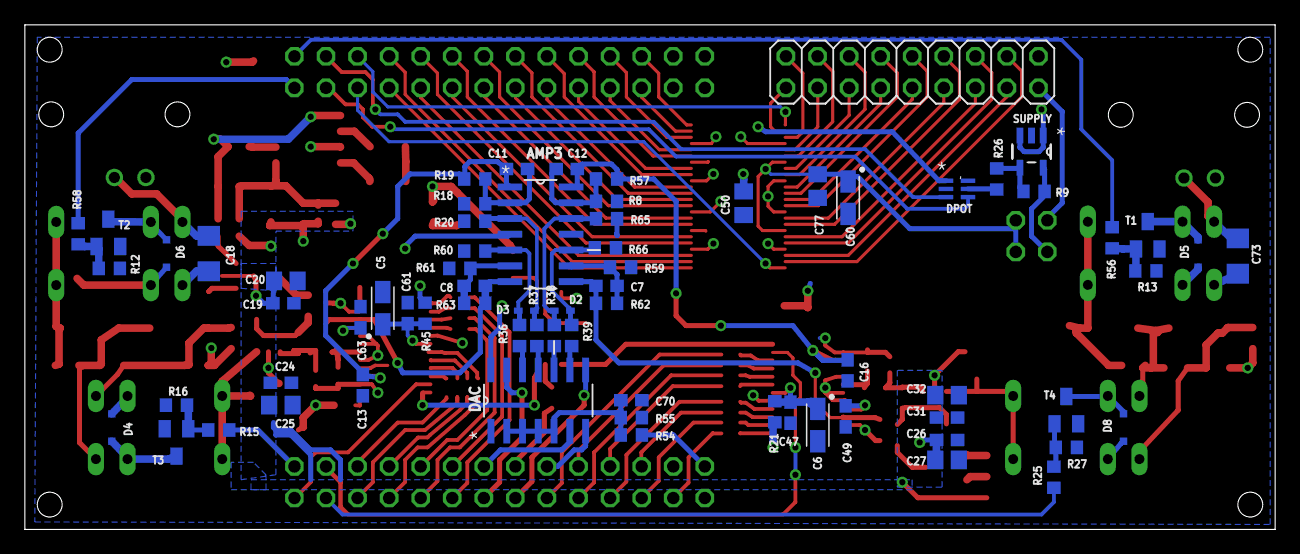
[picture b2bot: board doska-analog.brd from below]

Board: 2 copper layers, 100.6 x 40.6 mm, 142 parts (71 on the bottom side), 154 nets.

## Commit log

2013-06-25 Initial commit of QWave project
2013-06-26 Modified readme and added HACKING and COPYING
2013-06-26 Fixed short of internal layers on digital board (eagle bug).
2013-06-26 added link to PDF schematics
